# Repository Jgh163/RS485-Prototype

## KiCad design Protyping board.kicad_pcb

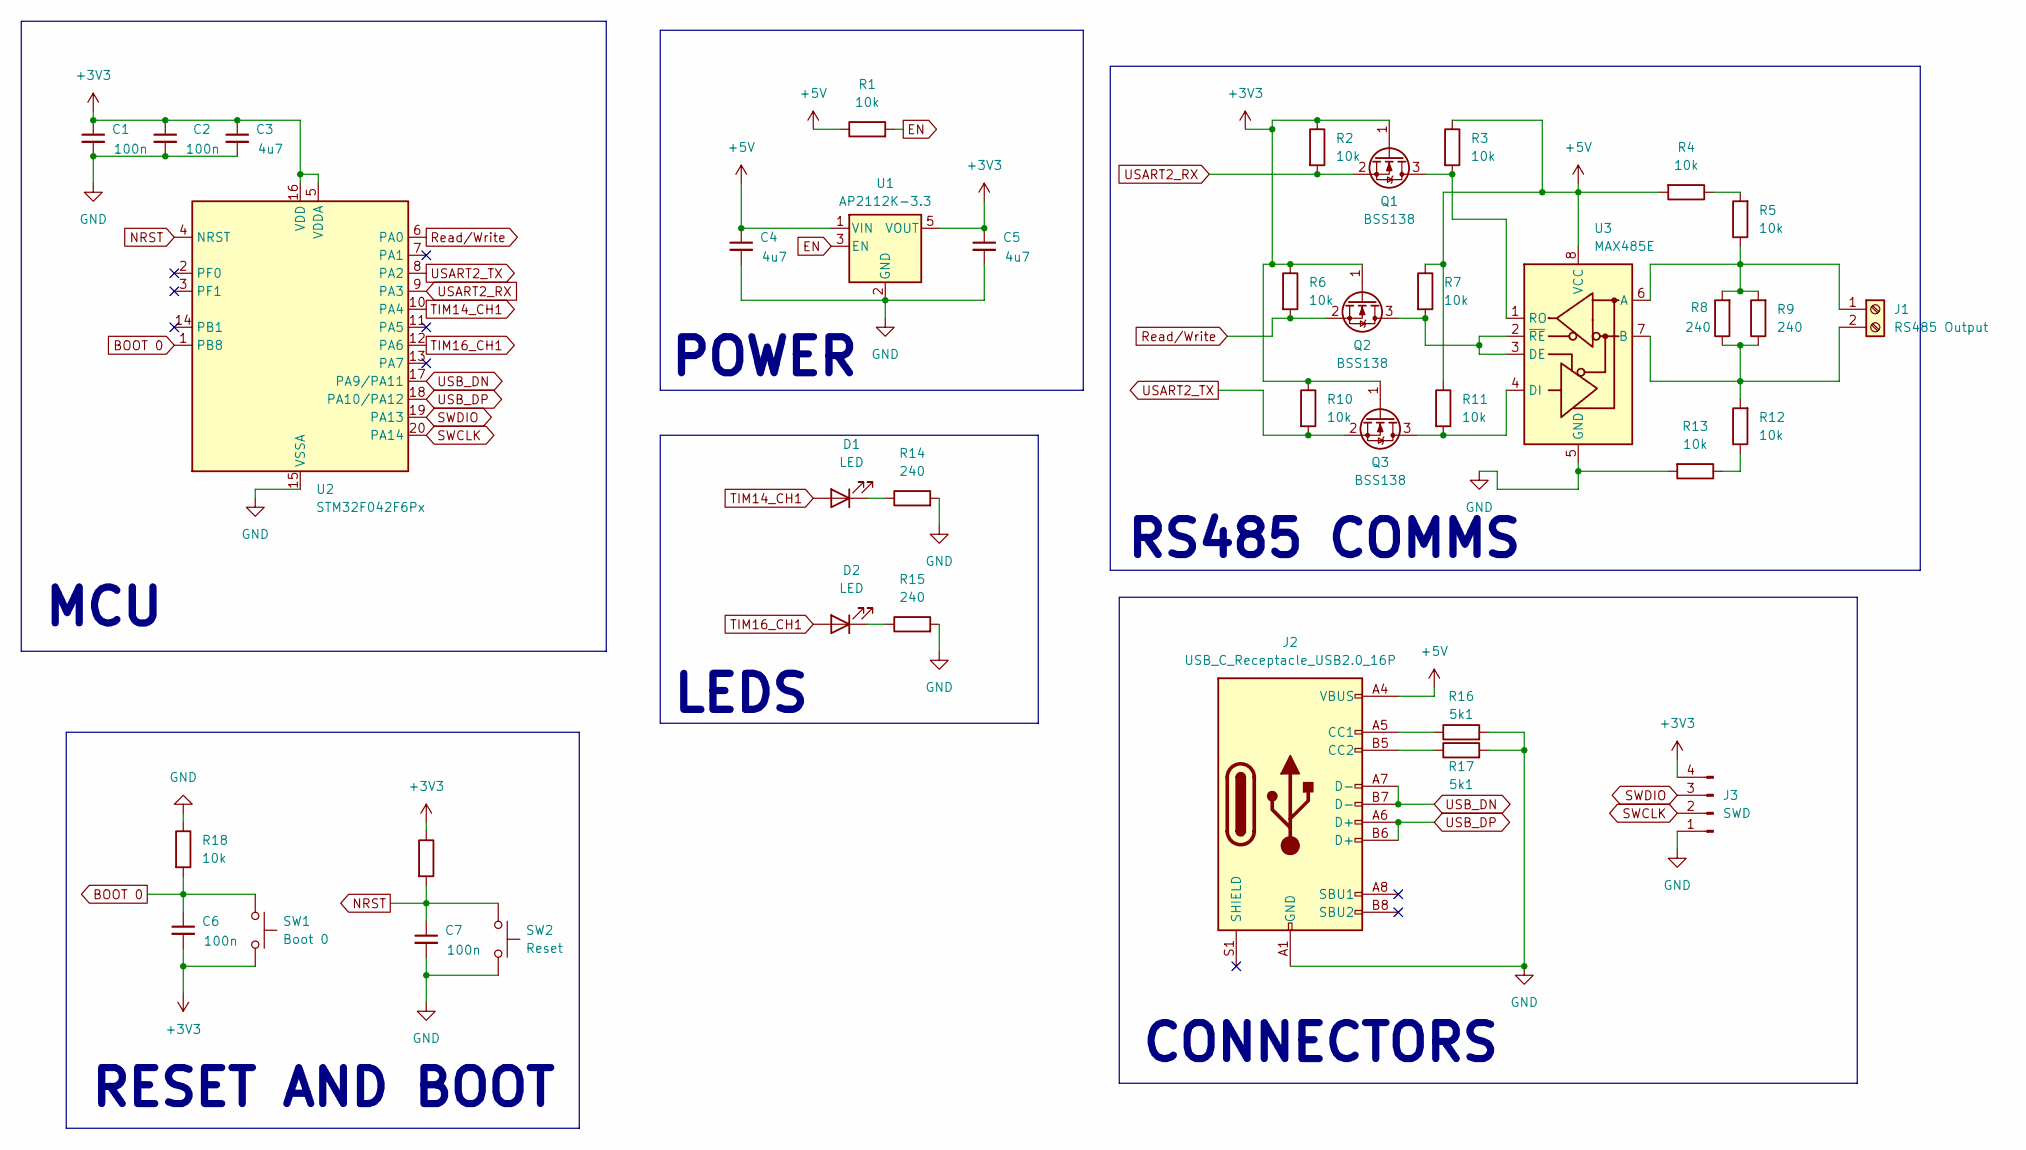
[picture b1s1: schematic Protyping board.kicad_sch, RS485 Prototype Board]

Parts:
C1, C2, C6, C7: 100n; C_0402_1005Metric; Part Number GRM155R62A104ME14D
C3, C4, C5: 4u7; C_1206_3216Metric; Part Number GRM31CC72A475ME11K
D1, D2: LED; LED_1206_3216Metric; Part Number LTST-C150GKT
J1: RS485 Output; TerminalBlock_Phoenix_MKDS-1,5-2-5.08_1x02_P5.08mm_Horizont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; Part Number 1711725
J2: USB_C_Receptacle_USB2.0_16P; USB_C_Receptacle_GCT_USB4105-xx-A_16P_TopMnt_Horizontal; Part Number USB4215-03-A
J3: SWD; PinHeader_1x04_P2.54mm_Vertical; Part Number 61300411121
Q1, Q2, Q3: BSS138; SOT-23-3; Part Number BSS138
R1, R2, R3, R4, R5, R6, R7, R10, R11, R12, R13, R18, R19: 10k; R_0603_1608Metric; Part Number CRCW060310K0FKEI
R8, R9, R14, R15: 240; R_0603_1608Metric; Part Number MCT06030C2400FP500
R16, R17: 5k1; R_0603_1608Metric; Part Number CRCW06035K10FKEBC
SW1: Boot 0; SW_Tactile_SPST_NO_Straight_CK_PTS636Sx25SMTRLFS; Part Number PTS636SM25JSMTR LFS
SW2: Reset; SW_Tactile_SPST_NO_Straight_CK_PTS636Sx25SMTRLFS; Part Number PTS636SM25JSMTR LFS
U1: AP2112K-3.3; SOT-23-5; Part Number AP2112K-3.3TRG1
U2: STM32F042F6Px; TSSOP-20_4.4x6.5mm_P0.65mm; Part Number STM32F042F6P6
U3: MAX485E; SOIC-8_3.9x4.9mm_P1.27mm; Part Number MAX485ECSA+T

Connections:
+3V3: C1.1, C2.1, C3.1, C5.1, C6.2, J3.4, Q1.1 (G), Q2.1 (G), Q3.1 (G), R2.1, R6.1, R10.1, R19.1, SW1.2, U1.5 (VOUT), U2.5 (VDDA), U2.16 (VDD)
+5V: C4.1, J2.A4 (VBUS), J2.A9 (VBUS), J2.B4 (VBUS), J2.B9 (VBUS), R1.1, R3.1, R4.2, R7.1, R11.1, U1.1 (VIN), U3.8 (VCC)
BOOT 0: C6.1, R18.2, SW1.1, U2.1 (PB8)
EN: R1.2, U1.3 (EN)
GND: C1.2, C2.2, C3.2, C4.2, C5.2, C7.2, J2.A1 (GND), J2.A12 (GND), J2.B1 (GND), J2.B12 (GND), J3.1, R13.2, R14.2, R15.2, R16.2, R17.2, R18.1, SW2.2, U1.2 (GND), U2.15 (VSSA), U3.5 (GND)
NRST: C7.1, R19.2, SW2.1, U2.4 (NRST)
unnamed: D1.1 (K), R14.1
unnamed: D2.1 (K), R15.1
unnamed: J1.1, R5.1, R8.2, R9.2, U3.6 (A)
unnamed: J1.2, R8.1, R9.1, R12.2, U3.7 (B)
unnamed: J2.A5 (CC1), R16.1
unnamed: J2.B5 (CC2), R17.1
unnamed: Q1.3 (D), R3.2, U3.1 (RO)
unnamed: Q2.3 (D), R7.2, U3.2 (~RE), U3.3 (DE)
unnamed: Q3.3 (D), R11.2, U3.4 (DI)
unnamed: R4.1, R5.2
unnamed: R12.1, R13.1
Read/Write: Q2.2 (S), R6.2, U2.6 (PA0)
SWCLK: J3.2, U2.20 (PA14)
SWDIO: J3.3, U2.19 (PA13)
TIM14_CH1: D1.2 (A), U2.10 (PA4)
TIM16_CH1: D2.2 (A), U2.12 (PA6)
USART2_RX: Q1.2 (S), R2.2, U2.9 (PA3)
USART2_TX: Q3.2 (S), R10.2, U2.8 (PA2)
USB_DN: J2.A7 (D-), J2.B7 (D-), U2.17 (PA9/PA11)
USB_DP: J2.A6 (D+), J2.B6 (D+), U2.18 (PA10/PA12)

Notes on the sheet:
POWER
LEDS
MCU
RESET AND BOOT
CONNECTORS
RS485 COMMS

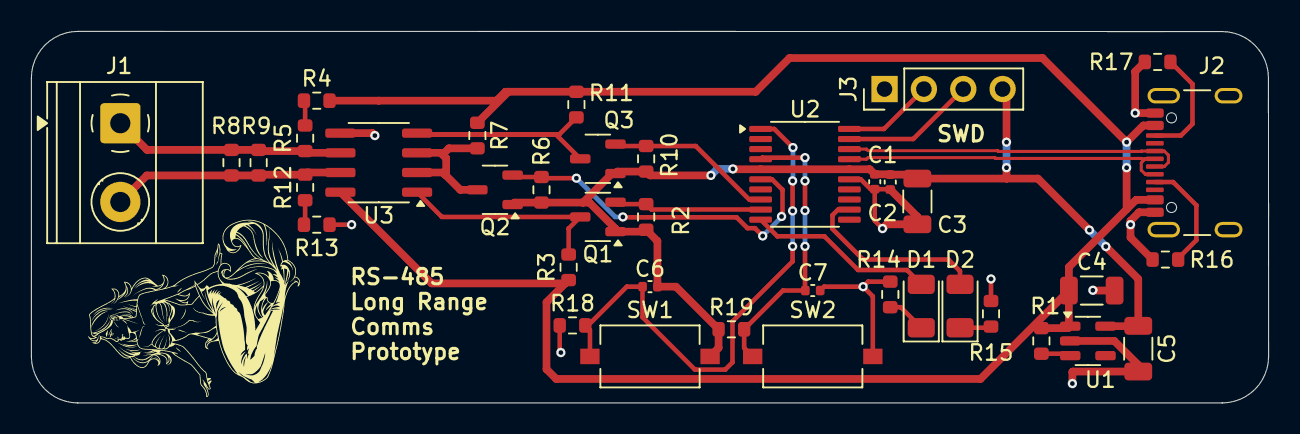
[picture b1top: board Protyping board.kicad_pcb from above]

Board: 2 copper layers, 79.8 x 24.0 mm, 39 parts (0 on the bottom side), 26 nets.
